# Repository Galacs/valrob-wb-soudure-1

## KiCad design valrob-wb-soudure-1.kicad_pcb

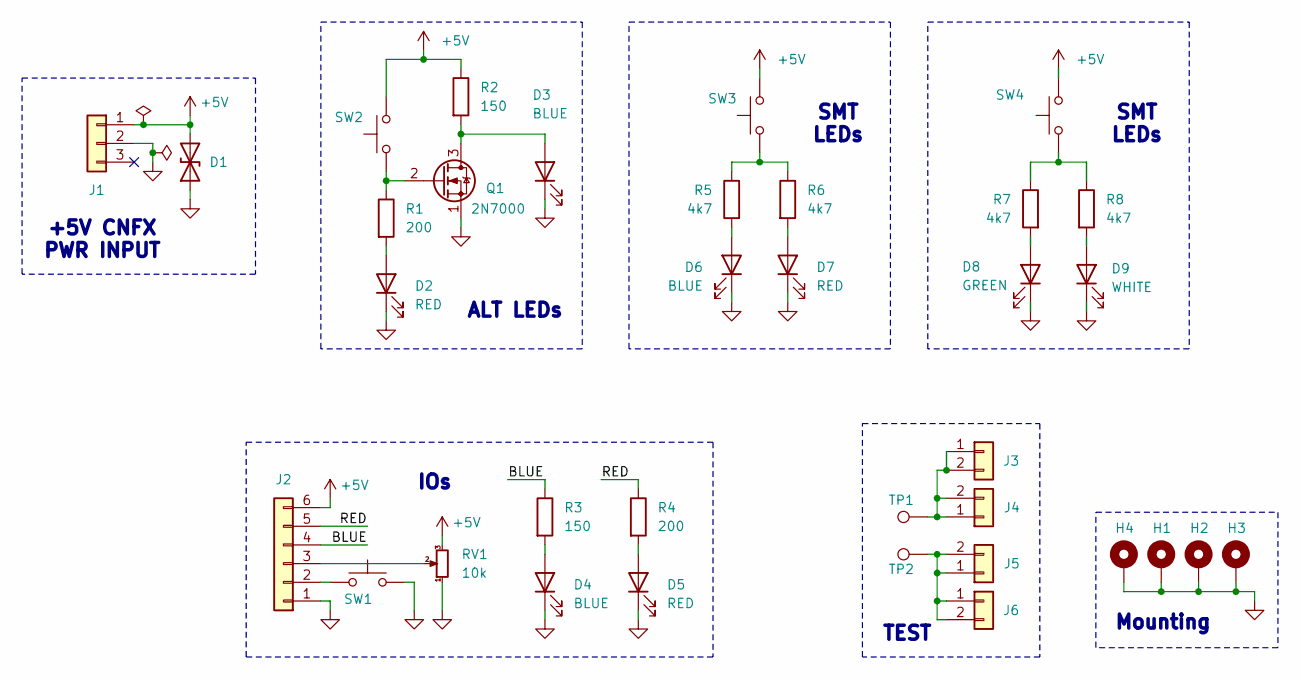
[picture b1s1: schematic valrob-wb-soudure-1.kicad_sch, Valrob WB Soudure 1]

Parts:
D1: D_TVS; D_DO-41_SOD81_P10.16mm_Horizontal; Manufacturer Part Number P4KE7.5CA; JLCPCB Part # C28485754
D2, D5: RED; LED_D3.0mm; Manufacturer Part Number XL-302SURD; JLCPCB Part # C2895470
D3, D4: BLUE; LED_D3.0mm; Manufacturer Part Number XL-302UBD; JLCPCB Part # C2895474
D6: BLUE; LED_1206_3216Metric_Pad1.42x1.75mm_HandSolder; Manufacturer Part Number XL-3216UBC; JLCPCB Part # C965827
D7: RED; LED_1206_3216Metric_Pad1.42x1.75mm_HandSolder; Manufacturer Part Number XL-3216UBC; JLCPCB Part # C965822
D8: GREEN; LED_0805_2012Metric; Manufacturer Part Number KT-0805G; JLCPCB Part # C2297
D9: WHITE; LED_0603_1608Metric; Manufacturer Part Number KT-0603W; JLCPCB Part # C2290
H1, H2, H3, H4: MountingHole_Pad; MountingHole_3.2mm_M3_Pad_Via
J1: Conn_01x03; JST_XH_B3B-XH-A_1x03_P2.50mm_Vertical; Manufacturer Part Number B3B-XH-A(LF)(SN); JLCPCB Part # C144394
J2: Conn_01x06; JST_XH_B6B-XH-A_1x06_P2.50mm_Vertical; Manufacturer Part Number B6B-XH-A(LF)(SN); JLCPCB Part # C144397
J3, J6: Conn_01x02; JST_XH_B2B-XH-A_1x02_P2.50mm_Vertical; Manufacturer Part Number B2B-XH-A-R(LF)(SN); JLCPCB Part # C495685
J4, J5: Conn_01x02; TerminalBlock_Phoenix_MKDS-1,5-2-5.08_1x02_P5.08mm_Horizont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; Manufacturer Part Number WJ500V-5.08-2P; JLCPCB Part # C8465
Q1: 2N7000; TO-92_Inline; Manufacturer Part Number 2N7000-TA; JLCPCB Part # C2910414
R1, R4: 200; R_Axial_DIN0207_L6.3mm_D2.5mm_P10.16mm_Horizontal; Manufacturer Part Number MFR-25FTE52-200R; JLCPCB Part # C138210
R2, R3: 150; R_Axial_DIN0207_L6.3mm_D2.5mm_P10.16mm_Horizontal; Manufacturer Part Number MFR-25FTE52-150R; JLCPCB Part # C172973
R5, R6, R7, R8: 4k7; R_1206_3216Metric_Pad1.30x1.75mm_HandSolder; Manufacturer Part Number 1206W4J0472T5E; JLCPCB Part # C26043
RV1: 10k; Potentiometer_Alps_RK09Y11_Single_Horizontal; Manufacturer Part Number RK09Y11L0001; JLCPCB Part # C470717
SW1, SW2, SW3: SW_Push; SW_SPST_Omron_B3F-40xx; Manufacturer Part Number B3F-4055; JLCPCB Part # C84931
SW4: SW_Push; SW_SPST_TS-1088-xR020; Manufacturer Part Number TS-1088-AR02016; JLCPCB Part # C720477
TP1, TP2: TestPoint; TestPoint_Loop_D3.50mm_Drill1.4mm_Beaded; Manufacturer Part Number RH-5011; JLCPCB Part # C5199814

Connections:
+5V: D1.2 (A2), J1.1, J2.6, R2.1, RV1.3, SW2.1, SW3.1, SW4.1
/BLUE: J2.4, R3.1
/RED: J2.5, R4.1
GND: D1.1 (A1), D2.1 (K), D3.1 (K), D4.1 (K), D5.1 (K), D6.1 (K), D7.1 (K), D8.1 (K), D9.1 (K), H1.1 (1_1), H2.1 (1_1), H3.1 (1_1), H4.1 (1_1), J1.2, J2.1, Q1.1 (S), RV1.1, SW1.2
unnamed: D2.2 (A), R1.2
unnamed: D3.2 (A), Q1.3 (D), R2.2
unnamed: D4.2 (A), R3.2
unnamed: D5.2 (A), R4.2
unnamed: D6.2 (A), R5.2
unnamed: D7.2 (A), R6.2
unnamed: D8.2 (A), R7.2
unnamed: D9.2 (A), R8.2
unnamed: J2.2, SW1.1
unnamed: J2.3, RV1.2
unnamed: J3.1, J3.2, J4.1, J4.2, TP1.1 (1_1)
unnamed: J5.1, J5.2, J6.1, J6.2, TP2.1 (1_1)
unnamed: Q1.2 (G), R1.1, SW2.2
unnamed: R5.1, R6.1, SW3.2
unnamed: R7.1, R8.1, SW4.2

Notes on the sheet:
SMT LEDs
Mounting
IOs
+5V CNFX PWR INPUT
ALT LEDs
TEST

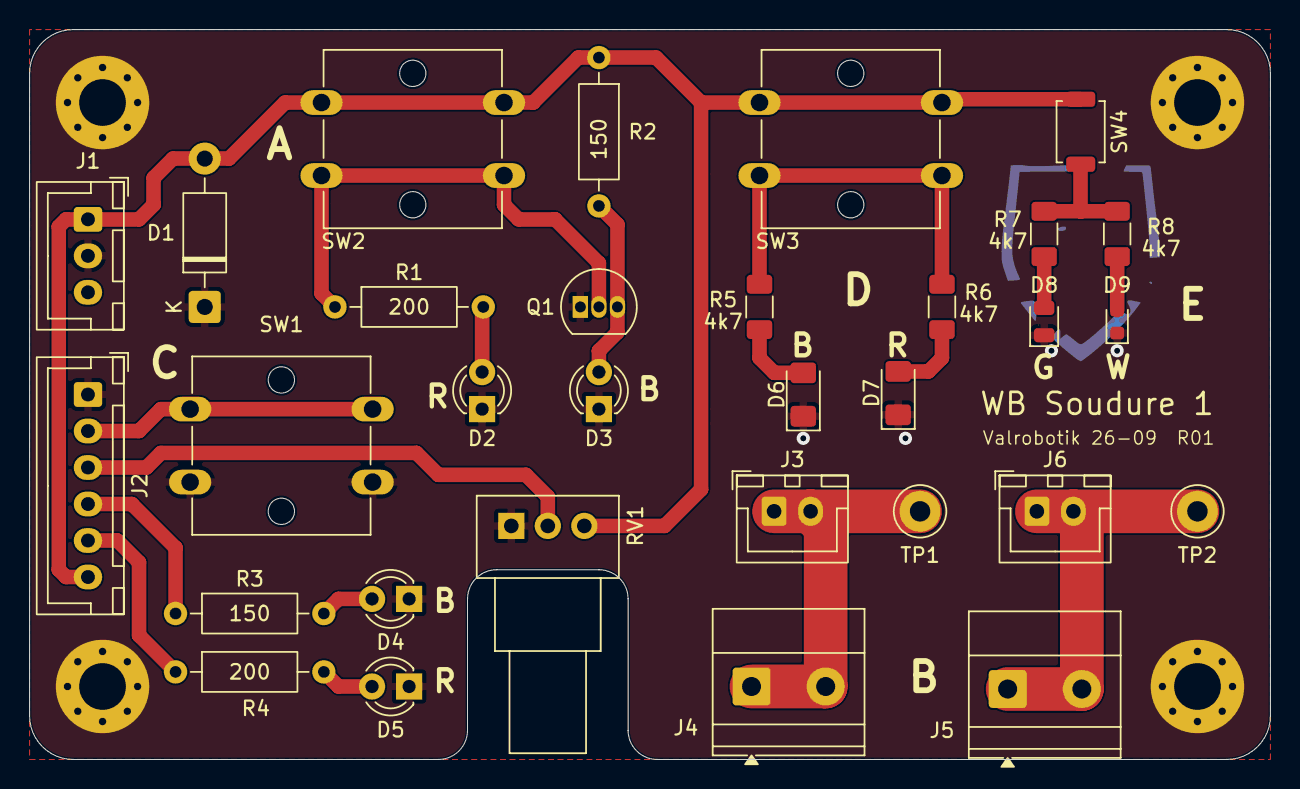
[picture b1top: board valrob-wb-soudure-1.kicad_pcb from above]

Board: 2 copper layers, 85.0 x 50.0 mm, 35 parts (0 on the bottom side), 19 nets.

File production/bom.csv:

Designator,Footprint,Quantity,Value,LCSC Part #
D1,D_DO-41_SOD81_P10.16mm_Horizontal,1,D_TVS,C28485754
"D2, D5",LED_D3.0mm,2,RED,C2895470
"D3, D4",LED_D3.0mm,2,BLUE,C2895474
D6,1206,1,BLUE,C965827
D7,1206,1,RED,C965822
D8,0805,1,GREEN,C2297
D9,0603,1,WHITE,C2290
J1,JST_XH_B3B-XH-A_1x03_P2.50mm_Vertical,1,Conn_01x03,C144394
J2,JST_XH_B6B-XH-A_1x06_P2.50mm_Vertical,1,Conn_01x06,C144397
"J3, J6",JST_XH_B2B-XH-A_1x02_P2.50mm_Vertical,2,Conn_01x02,C495685
"J4, J5","TerminalBlock_Phoenix_MKDS-1,5-2-5.08_1x02_P5.08mm_Horizontal",2,Conn_01x02,
Q1,TO-92_Inline,1,2N7000,C2910414
"R1, R4",R_Axial_DIN0207_L6.3mm_D2.5mm_P10.16mm_Horizontal,2,200,C138210
"R2, R3",R_Axial_DIN0207_L6.3mm_D2.5mm_P10.16mm_Horizontal,2,150,C172973
"R5, R6, R7, R8",1206,4,4k7,C26043
RV1,Potentiometer_Alps_RK09Y11_Single_Horizontal,1,10k,C470717
"SW1, SW2, SW3",SW_SPST_Omron_B3F-40xx,3,SW_Push,C84931
SW4,SW_SPST_TS-1088-xR020,1,SW_Push,C720477
"TP1, TP2",TestPoint_Loop_D3.50mm_Drill1.4mm_Beaded,2,TestPoint,C5199814
